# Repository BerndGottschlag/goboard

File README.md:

# GoBoard

This project contains the PCB design and the firmware for a compact modular
wireless mechanical keyboard.

## License

All hardware designes are licensed under the CERN Open Hardware License v1.2.

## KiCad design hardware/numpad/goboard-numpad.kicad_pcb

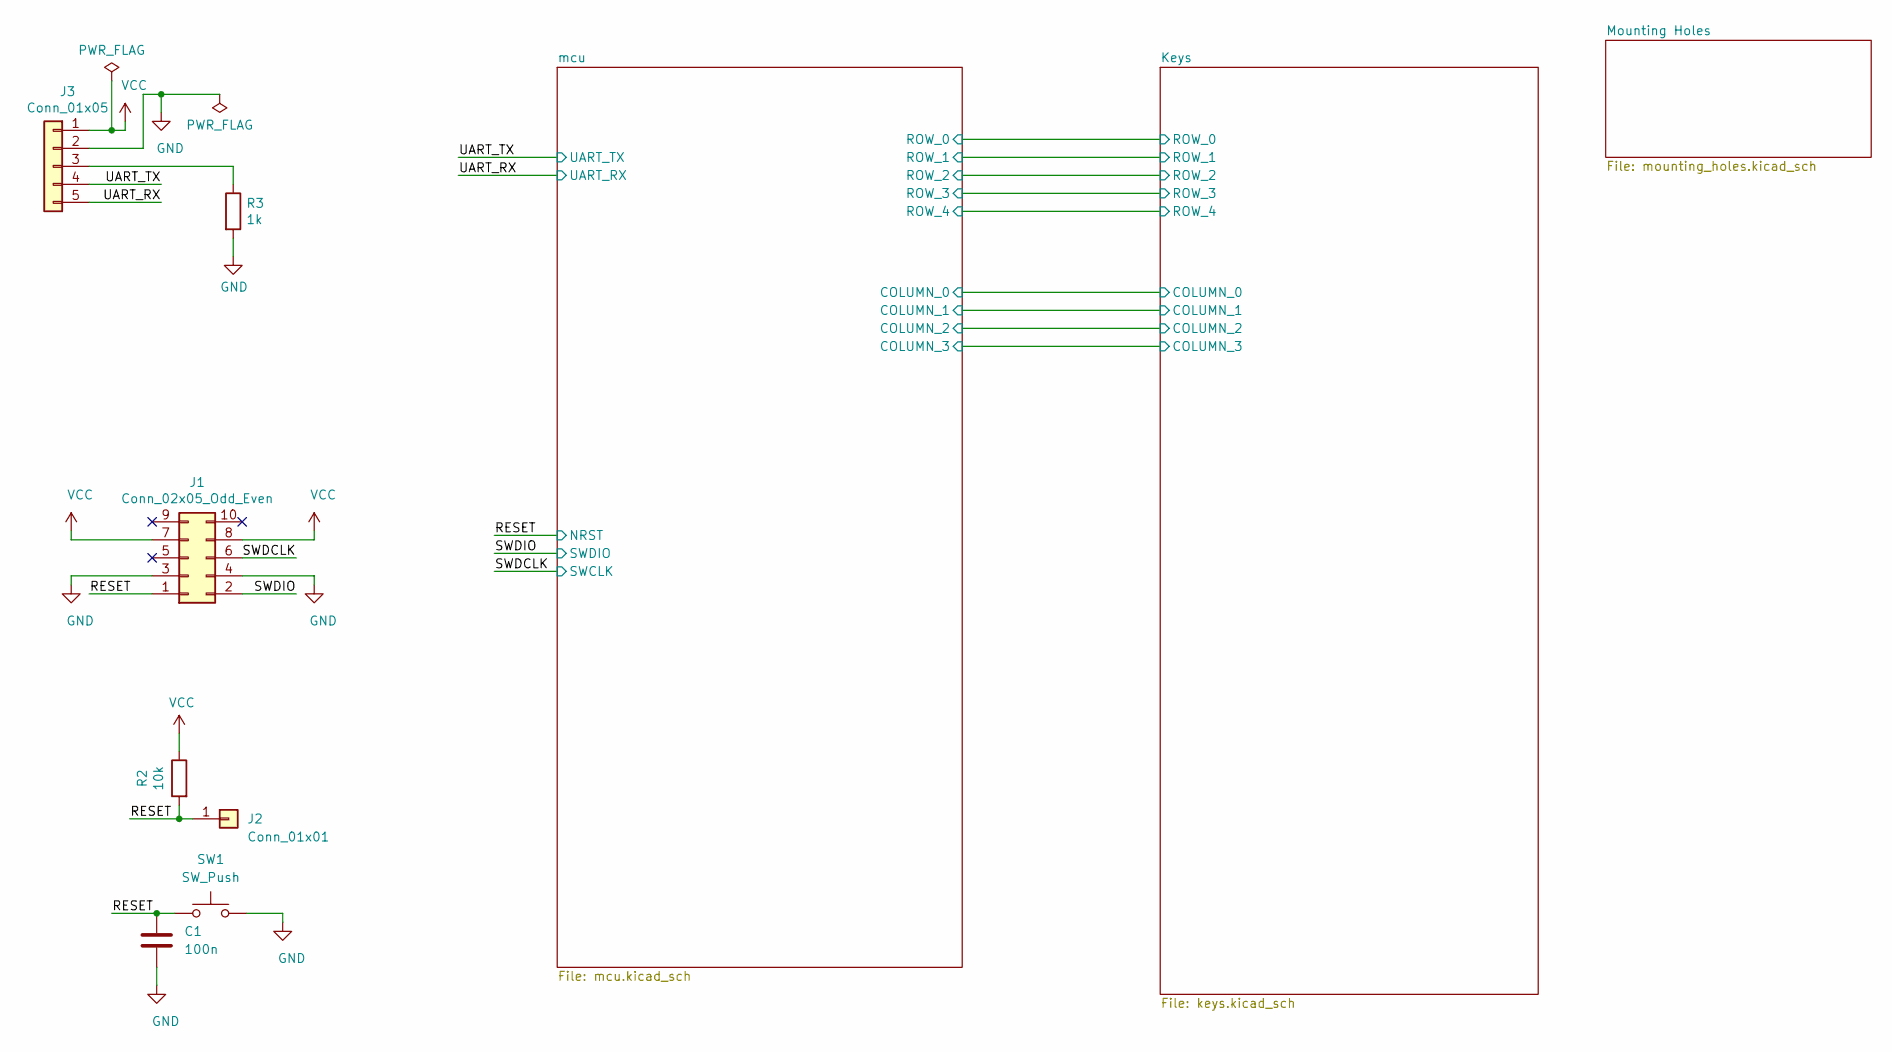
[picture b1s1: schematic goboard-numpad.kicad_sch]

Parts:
C1: 100n; C_0603_1608Metric_Pad1.08x0.95mm_HandSolder; Part Name AVX 0603YC104MAT4A; Mouser 581-0603YC104MAT4A
J1: Conn_02x05_Odd_Even; programming_port_st_link_clone_without_silkscreen_outline
J2: Conn_01x01; PinHeader_1x01_P2.54mm_Vertical
J3: Conn_01x05; PinHeader_1x05_P2.54mm_Vertical
R2: 10k; R_0603_1608Metric_Pad0.98x0.95mm_HandSolder
R3: 1k; R_0603_1608Metric_Pad0.98x0.95mm_HandSolder
SW1: SW_Push; SW_SPST_CK_RS282G05A3; Part Name PTS636 SM25 SMTR LFS; Mouser 611-PTS636SM25SMTRLF

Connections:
/RESET: C1.1, J1.1, J2.1, R2.2, SW1.1; also elsewhere on the board
/SWDCLK: J1.6; also elsewhere on the board
/SWDIO: J1.2; also elsewhere on the board
/UART_RX: J3.5; also elsewhere on the board
/UART_TX: J3.4; also elsewhere on the board
GND: C1.2, J1.3, J1.4, J3.2, R3.2, SW1.2; also elsewhere on the board
unnamed: J3.3, R3.1
VCC: J1.7, J1.8, J3.1, R2.1; also elsewhere on the board

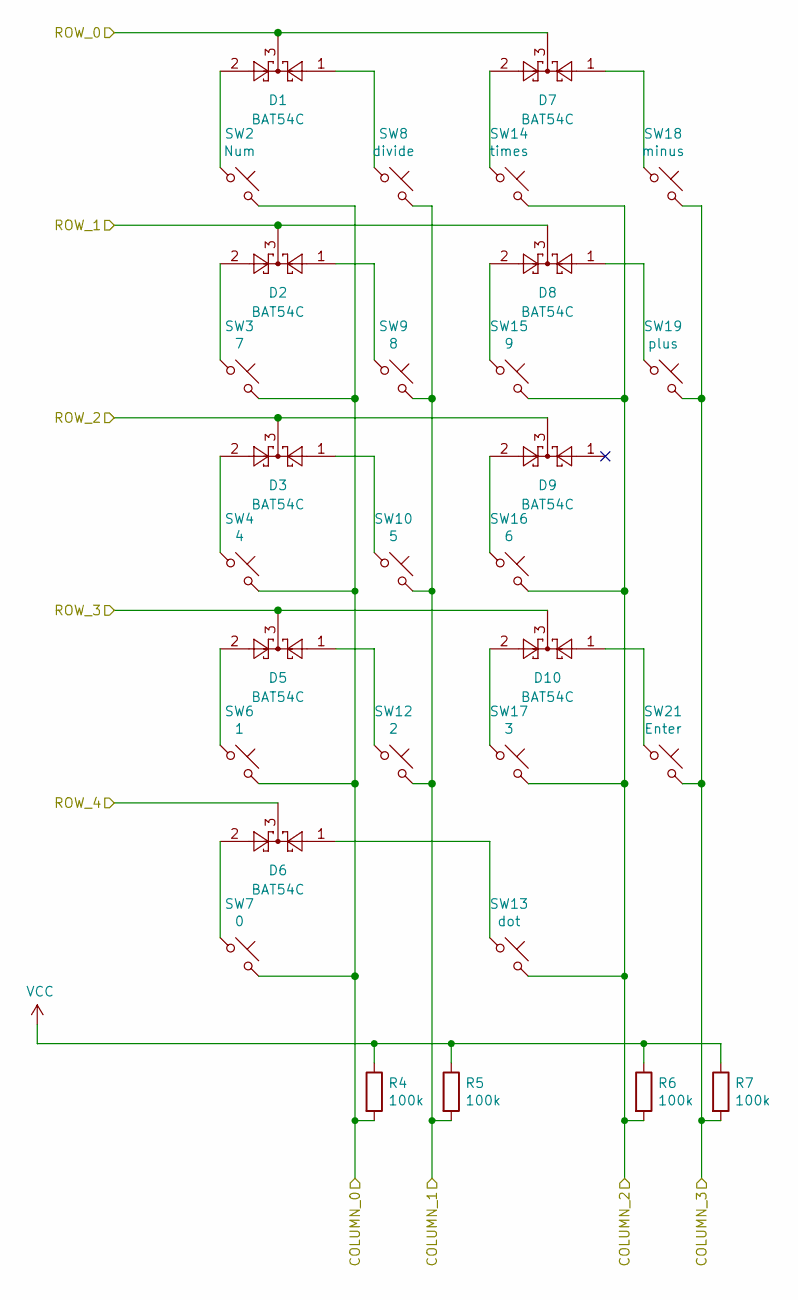
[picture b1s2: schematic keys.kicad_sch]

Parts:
D1, D2, D3, D5, D6, D7, D8, D9, D10: BAT54C; SOT-23; Part Name BAT54C; Mouser 241-BAT54C_R1_00001
R4, R5, R6, R7: 100k; R_0603_1608Metric_Pad0.98x0.95mm_HandSolder
SW2: Num; SW_Cherry_MX_1.00u_PCB; Part Name MX1A-E1NW; Mouser 540-MX1A-E1NW
SW3: 7; SW_Cherry_MX_1.00u_PCB; Part Name MX1A-E1NW; Mouser 540-MX1A-E1NW
SW4: 4; SW_Cherry_MX_1.00u_PCB; Part Name MX1A-E1NW; Mouser 540-MX1A-E1NW
SW6: 1; SW_Cherry_MX_1.00u_PCB; Part Name MX1A-E1NW; Mouser 540-MX1A-E1NW
SW7: 0; SW_Cherry_MX_2.00u_PCB; Part Name MX1A-E1NW; Mouser 540-MX1A-E1NW
SW8: divide; SW_Cherry_MX_1.00u_PCB; Part Name MX1A-E1NW; Mouser 540-MX1A-E1NW
SW9: 8; SW_Cherry_MX_1.00u_PCB; Part Name MX1A-E1NW; Mouser 540-MX1A-E1NW
SW10: 5; SW_Cherry_MX_1.00u_PCB; Part Name MX1A-E1NW; Mouser 540-MX1A-E1NW
SW12: 2; SW_Cherry_MX_1.00u_PCB; Part Name MX1A-E1NW; Mouser 540-MX1A-E1NW
SW13: dot; SW_Cherry_MX_1.00u_PCB; Part Name MX1A-E1NW; Mouser 540-MX1A-E1NW
SW14: times; SW_Cherry_MX_1.00u_PCB; Part Name MX1A-E1NW; Mouser 540-MX1A-E1NW
SW15: 9; SW_Cherry_MX_1.00u_PCB; Part Name MX1A-E1NW; Mouser 540-MX1A-E1NW
SW16: 6; SW_Cherry_MX_1.00u_PCB; Part Name MX1A-E1NW; Mouser 540-MX1A-E1NW
SW17: 3; SW_Cherry_MX_1.00u_PCB; Part Name MX1A-E1NW; Mouser 540-MX1A-E1NW
SW18: minus; SW_Cherry_MX_1.00u_PCB; Part Name MX1A-E1NW; Mouser 540-MX1A-E1NW
SW19: plus; SW_Cherry_MX_2.00u_PCB; Part Name MX1A-E1NW; Mouser 540-MX1A-E1NW
SW21: Enter; SW_Cherry_MX_2.00u_PCB; Part Name MX1A-E1NW; Mouser 540-MX1A-E1NW

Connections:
/Keys/COLUMN_0: R4.2, SW2.2, SW3.2, SW4.2, SW6.2, SW7.2; also elsewhere on the board
/Keys/COLUMN_1: R5.2, SW8.2, SW9.2, SW10.2, SW12.2; also elsewhere on the board
/Keys/COLUMN_2: R6.2, SW13.2, SW14.2, SW15.2, SW16.2, SW17.2; also elsewhere on the board
/Keys/COLUMN_3: R7.2, SW18.2, SW19.2, SW21.2; also elsewhere on the board
/Keys/ROW_0: D1.3, D7.3; also elsewhere on the board
/Keys/ROW_1: D2.3, D8.3; also elsewhere on the board
/Keys/ROW_2: D3.3, D9.3; also elsewhere on the board
/Keys/ROW_3: D5.3, D10.3; also elsewhere on the board
/Keys/ROW_4: D6.3; also elsewhere on the board
unnamed: D1.1, SW8.1
unnamed: D1.2, SW2.1
unnamed: D2.1, SW9.1
unnamed: D2.2, SW3.1
unnamed: D3.1, SW10.1
unnamed: D3.2, SW4.1
unnamed: D5.1, SW12.1
unnamed: D5.2, SW6.1
unnamed: D6.1, SW13.1
unnamed: D6.2, SW7.1
unnamed: D7.1, SW18.1
unnamed: D7.2, SW14.1
unnamed: D8.1, SW19.1
unnamed: D8.2, SW15.1
unnamed: D9.2, SW16.1
unnamed: D10.1, SW21.1
unnamed: D10.2, SW17.1
VCC: R4.1, R5.1, R6.1, R7.1; also elsewhere on the board

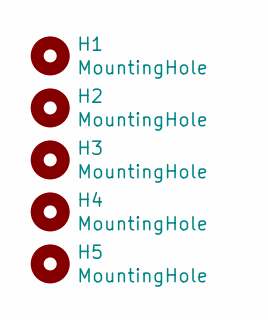
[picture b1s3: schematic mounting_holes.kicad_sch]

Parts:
H1, H2, H3, H4, H5: MountingHole; MountingHole_2.2mm_M2_Pad

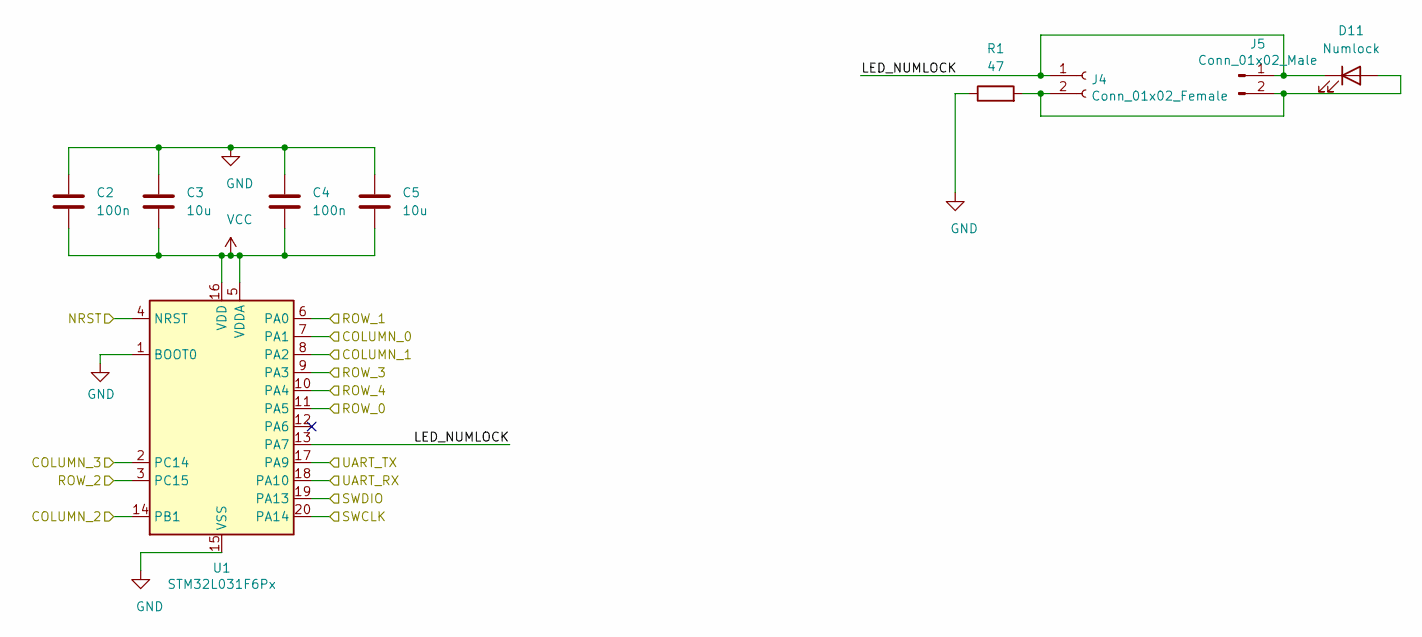
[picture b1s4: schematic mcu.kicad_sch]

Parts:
C2, C4: 100n; C_0603_1608Metric_Pad1.08x0.95mm_HandSolder; Part Name AVX 0603YC104MAT4A; Mouser 581-0603YC104MAT4A
C3, C5: 10u; C_0805_2012Metric; Part Name Samsung CL21A106KOQNNNG; Mouser 187-CL21A106KOQNNNG
D11: Numlock; D_0603_1608Metric_Pad1.05x0.95mm_HandSolder; Part Name 150060SS75000; Mouser 710-150060SS75000
J4: Conn_01x02_Female; PinSocket_1x02_P2.00mm_Vertical
J5: Conn_01x02_Male; PinSocket_1x02_P2.00mm_Vertical
R1: 47; R_0603_1608Metric_Pad0.98x0.95mm_HandSolder
U1: STM32L031F6Px; TSSOP-20_4.4x6.5mm_P0.65mm; Part Name STM32L031F6P7; Mouser 511-STM32L031F6P7

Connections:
/Keys/COLUMN_0: U1.7 (PA1); also elsewhere on the board
/Keys/COLUMN_1: U1.8 (PA2); also elsewhere on the board
/Keys/COLUMN_2: U1.14 (PB1); also elsewhere on the board
/Keys/COLUMN_3: U1.2 (PC14); also elsewhere on the board
/Keys/ROW_0: U1.11 (PA5); also elsewhere on the board
/Keys/ROW_1: U1.6 (PA0); also elsewhere on the board
/Keys/ROW_2: U1.3 (PC15); also elsewhere on the board
/Keys/ROW_3: U1.9 (PA3); also elsewhere on the board
/Keys/ROW_4: U1.10 (PA4); also elsewhere on the board
/RESET: U1.4 (NRST); also elsewhere on the board
/SWDCLK: U1.20 (PA14); also elsewhere on the board
/SWDIO: U1.19 (PA13); also elsewhere on the board
/UART_RX: U1.18 (PA10); also elsewhere on the board
/UART_TX: U1.17 (PA9); also elsewhere on the board
/mcu/LED_NUMLOCK: D11.1 (K), J4.1, J5.1, U1.13 (PA7)
GND: C2.1, C3.1, C4.1, C5.1, R1.1, U1.1 (BOOT0), U1.15 (VSS); also elsewhere on the board
unnamed: D11.2 (A), J4.2, J5.2, R1.2
VCC: C2.2, C3.2, C4.2, C5.2, U1.5 (VDDA), U1.16 (VDD); also elsewhere on the board

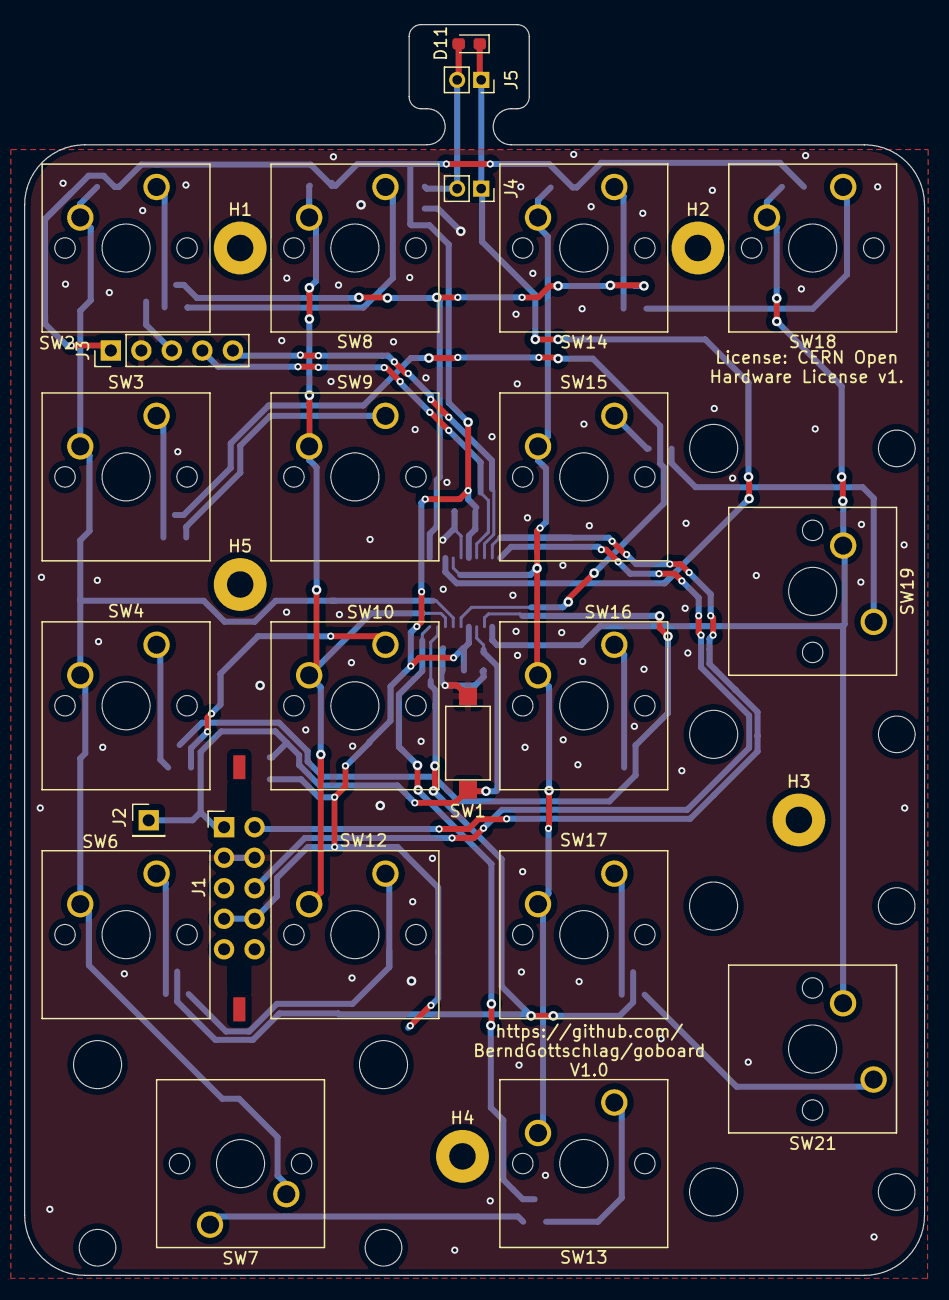
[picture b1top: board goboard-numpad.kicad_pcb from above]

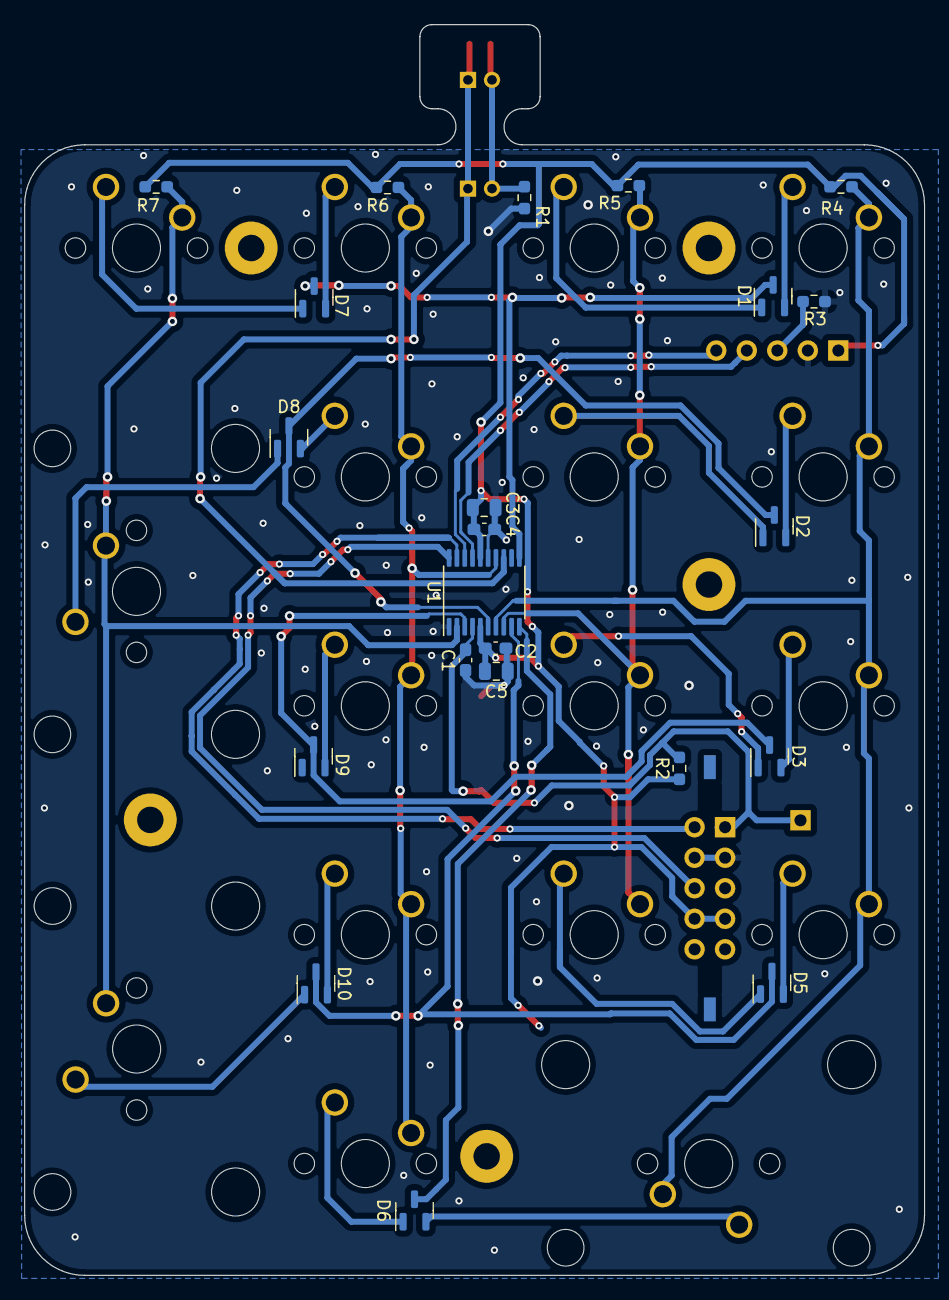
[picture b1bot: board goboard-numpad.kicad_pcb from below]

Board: 2 copper layers, 74.9 x 104.1 mm, 51 parts (22 on the bottom side), 36 nets.

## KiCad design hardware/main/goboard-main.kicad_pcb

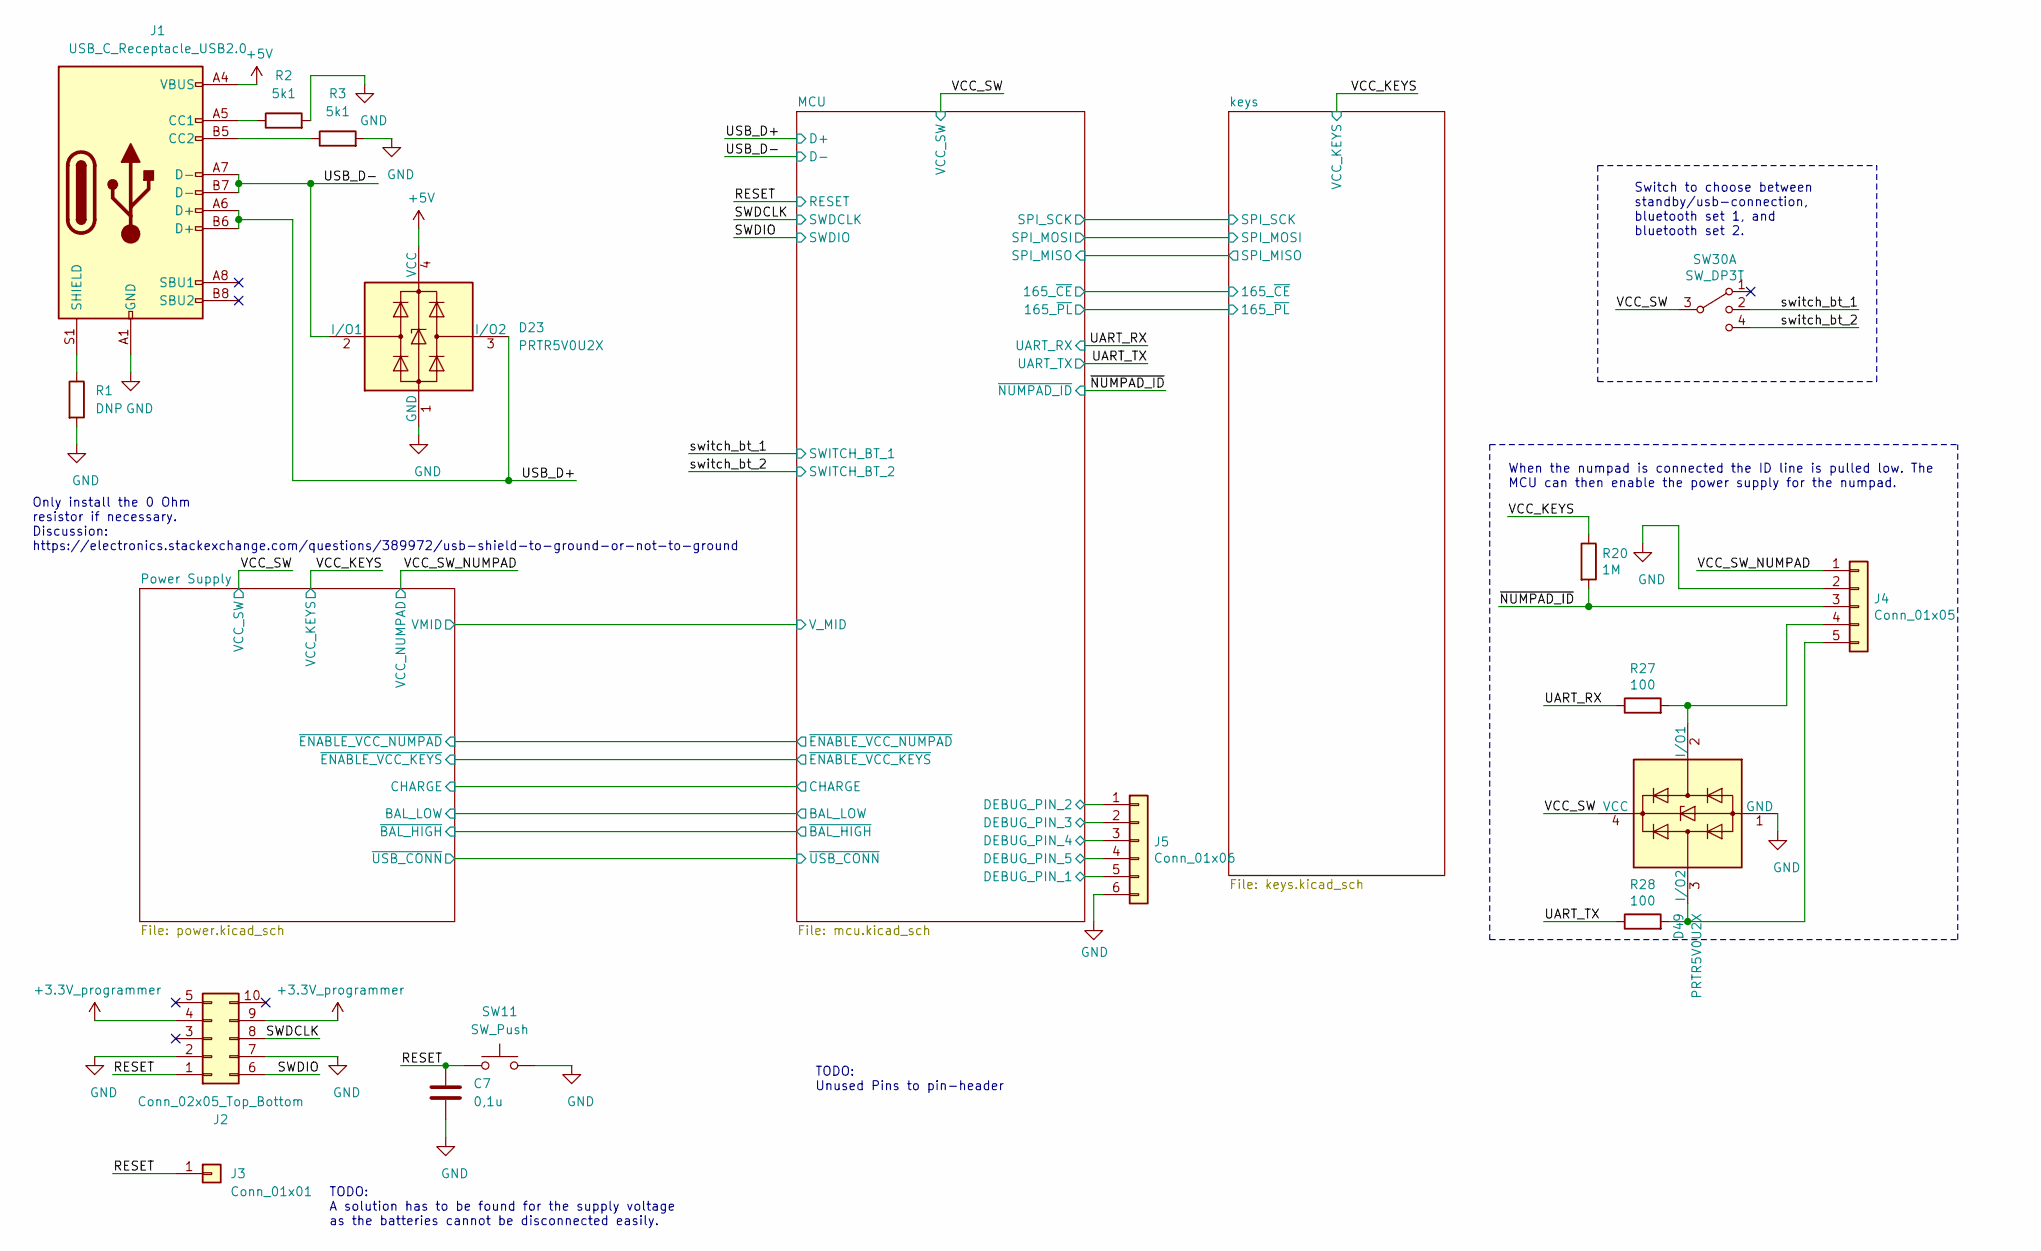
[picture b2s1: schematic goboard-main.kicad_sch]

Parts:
C7: 0,1u; C_0603_1608Metric_Pad1.08x0.95mm_HandSolder; Part Name 06033C104KAT4A; Mouser 581-06033C104KAT4A
D23, D49: PRTR5V0U2X; SOT-143; Part Name PRTR5V0U2X,215; Mouser 771-PRTR5V0U2X-T/R
J1: USB_C_Receptacle_USB2.0; USB_C_Receptale_JAE_DX07S016JA1R1500; Part Name DX07S016JA1R1500; Mouser 656-DX07S016JA1R1500
J2: Conn_02x05_Top_Bottom; programming_port_st_link_clone
J3: Conn_01x01; PinHeader_1x01_P2.54mm_Vertical
J4: Conn_01x05; PinHeader_1x05_P2.54mm_Vertical
J5: Conn_01x06; PinHeader_1x06_P2.54mm_Vertical
R1: DNP; R_0603_1608Metric_Pad0.98x0.95mm_HandSolder
R2, R3: 5k1; R_0603_1608Metric_Pad0.98x0.95mm_HandSolder
R20: 1M; R_0603_1608Metric_Pad0.98x0.95mm_HandSolder
R27, R28: 100; R_0603_1608Metric_Pad0.98x0.95mm_HandSolder
SW11: SW_Push; SW_SPST_CK_RS282G05A3; Part Name PTS636 SM25 SMTR LFS; Mouser 611-PTS636SM25SMTRLF
SW30: SW_DP3T; EG2315A; Part Name EG2315A; Mouser 612-EG2315A

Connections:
+5V: D23.4 (VCC), J1.A4 (VBUS), J1.A9 (VBUS), J1.B4 (VBUS), J1.B9 (VBUS); also elsewhere on the board
/MCU/DEBUG_PIN_1: J5.5; also elsewhere on the board
/MCU/DEBUG_PIN_2: J5.1; also elsewhere on the board
/MCU/DEBUG_PIN_3: J5.2; also elsewhere on the board
/MCU/DEBUG_PIN_4: J5.3; also elsewhere on the board
/MCU/DEBUG_PIN_5: J5.4; also elsewhere on the board
/RESET: C7.1, J2.1, J3.1, SW11.1; also elsewhere on the board
/SWDCLK: J2.8; also elsewhere on the board
/SWDIO: J2.6; also elsewhere on the board
/UART_RX: R27.1; also elsewhere on the board
/UART_TX: R28.1; also elsewhere on the board
/USB_D+: D23.3 (I/O2), J1.A6 (D+), J1.B6 (D+); also elsewhere on the board
/USB_D-: D23.2 (I/O1), J1.A7 (D-), J1.B7 (D-); also elsewhere on the board
/VCC_KEYS: R20.1; also elsewhere on the board
/VCC_SW: D49.4 (VCC), SW30.3; also elsewhere on the board
/VCC_SW_NUMPAD: J4.1; also elsewhere on the board
/switch_bt_1: SW30.2; also elsewhere on the board
/switch_bt_2: SW30.4; also elsewhere on the board
/~NUMPAD_ID: J4.3, R20.2; also elsewhere on the board
GND: C7.2, D23.1 (GND), D49.1 (GND), J1.A1 (GND), J1.A12 (GND), J1.B1 (GND), J1.B12 (GND), J2.2, J2.7, J4.2, J5.6, R1.2, R2.2, R3.2, SW11.2; also elsewhere on the board
unnamed: D49.2 (I/O1), J4.4, R27.2
unnamed: D49.3 (I/O2), J4.5, R28.2
unnamed: J1.A5 (CC1), R2.1
unnamed: J1.B5 (CC2), R3.1
unnamed: J1.S1 (SHIELD), R1.1

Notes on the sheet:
Only install the 0 Ohm resistor if necessary. Discussion: https://electronics.stackexchange.com/questions/389972/usb-shield-to-ground-or-not-to-ground
TODO: A solution has to be found for the supply voltage as the batteries cannot be disconnected easily.
TODO: Unused Pins to pin-header
When the numpad is connected the ID line is pulled low. The MCU can then enable the power supply for the numpad.
Switch to choose between standby/usb-connection, bluetooth set 1, and bluetooth set 2.

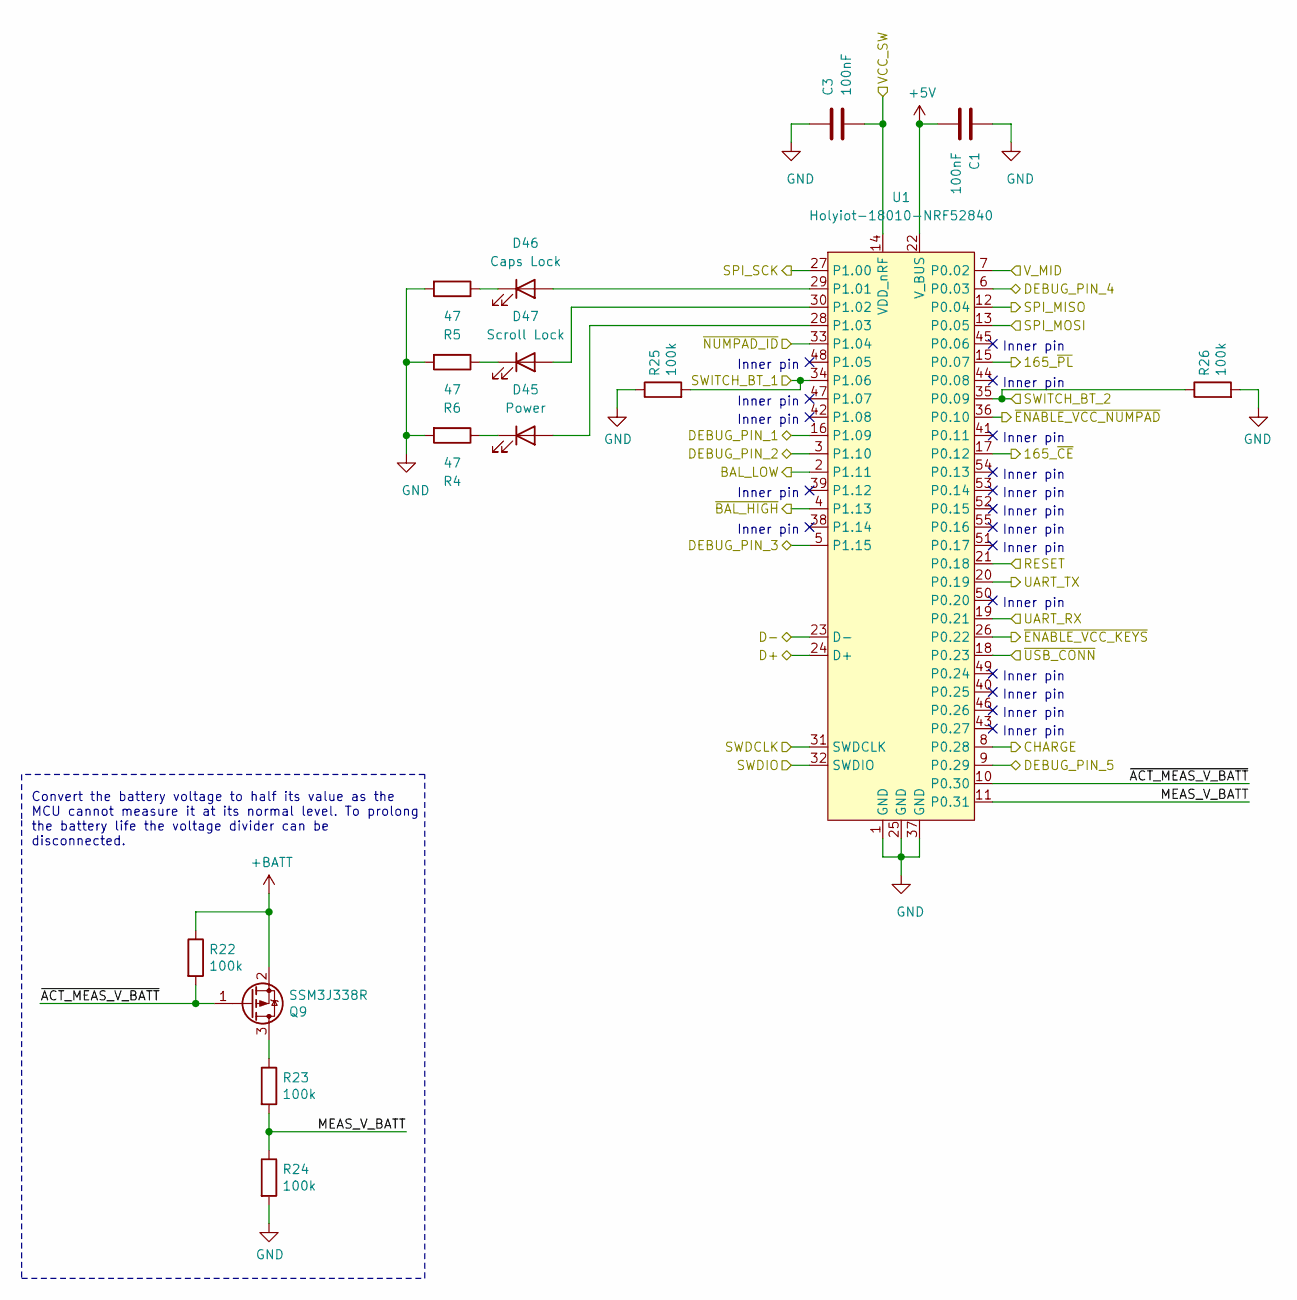
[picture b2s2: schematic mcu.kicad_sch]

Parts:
C1, C3: 100nF; C_0603_1608Metric_Pad1.08x0.95mm_HandSolder; Part Name 06033C104KAT4A; Mouser 581-06033C104KAT4A
D45: Power; D_0603_1608Metric_Pad1.05x0.95mm_HandSolder; Part Name 150060SS75000; Mouser 710-150060SS75000
D46: Caps Lock; D_0603_1608Metric_Pad1.05x0.95mm_HandSolder; Part Name 150060SS75000; Mouser 710-150060SS75000
D47: Scroll Lock; D_0603_1608Metric_Pad1.05x0.95mm_HandSolder; Part Name 150060SS75000; Mouser 710-150060SS75000
Q9: SSM3J338R; SOT-23_Handsoldering; Part Name Toshiba SSM3J338R; Mouser 757-SSM3J338RLF
R4, R5, R6: 47; R_0603_1608Metric_Pad0.98x0.95mm_HandSolder
R22, R23, R24, R25, R26: 100k; R_0603_1608Metric_Pad0.98x0.95mm_HandSolder
U1: Holyiot-18010-NRF52840

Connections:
+5V: C1.2, U1.22 (V_BUS); also elsewhere on the board
+BATT: Q9.2 (S), R22.1; also elsewhere on the board
/MCU/165_~CE: U1.17 (P0.12); also elsewhere on the board
/MCU/165_~PL: U1.15 (P0.07); also elsewhere on the board
/MCU/BAL_LOW: U1.2 (P1.11); also elsewhere on the board
/MCU/CHARGE: U1.8 (P0.28); also elsewhere on the board
/MCU/DEBUG_PIN_1: U1.16 (P1.09); also elsewhere on the board
/MCU/DEBUG_PIN_2: U1.3 (P1.10); also elsewhere on the board
/MCU/DEBUG_PIN_3: U1.5 (P1.15); also elsewhere on the board
/MCU/DEBUG_PIN_4: U1.6 (P0.03); also elsewhere on the board
/MCU/DEBUG_PIN_5: U1.9 (P0.29); also elsewhere on the board
/MCU/MEAS_V_BATT: R23.2, R24.1, U1.11 (P0.31)
/MCU/SPI_MISO: U1.12 (P0.04); also elsewhere on the board
/MCU/SPI_MOSI: U1.13 (P0.05); also elsewhere on the board
/MCU/SPI_SCK: U1.27 (P1.00); also elsewhere on the board
/MCU/V_MID: U1.7 (P0.02); also elsewhere on the board
/MCU/~ACT_MEAS_V_BATT: Q9.1 (G), R22.2, U1.10 (P0.30)
/MCU/~BAL_HIGH: U1.4 (P1.13); also elsewhere on the board
/MCU/~ENABLE_VCC_KEYS: U1.26 (P0.22); also elsewhere on the board
/MCU/~ENABLE_VCC_NUMPAD: U1.36 (P0.10); also elsewhere on the board
/MCU/~USB_CONN: U1.18 (P0.23); also elsewhere on the board
/RESET: U1.21 (P0.18); also elsewhere on the board
/SWDCLK: U1.31 (SWDCLK); also elsewhere on the board
/SWDIO: U1.32 (SWDIO); also elsewhere on the board
/UART_RX: U1.19 (P0.21); also elsewhere on the board
/UART_TX: U1.20 (P0.19); also elsewhere on the board
/USB_D+: U1.24 (D+); also elsewhere on the board
/USB_D-: U1.23 (D-); also elsewhere on the board
/VCC_SW: C3.2, U1.14 (VDD_nRF); also elsewhere on the board
/switch_bt_1: R25.2, U1.34 (P1.06); also elsewhere on the board
/switch_bt_2: R26.1, U1.35 (P0.09); also elsewhere on the board
/~NUMPAD_ID: U1.33 (P1.04); also elsewhere on the board
GND: C1.1, C3.1, R4.2, R5.2, R6.2, R24.2, R25.1, R26.2, U1.1 (GND), U1.25 (GND), U1.37 (GND); also elsewhere on the board
unnamed: D45.1 (K), R4.1
unnamed: D45.2 (A), U1.28 (P1.03)
unnamed: D46.1 (K), R5.1
unnamed: D46.2 (A), U1.29 (P1.01)
unnamed: D47.1 (K), R6.1
unnamed: D47.2 (A), U1.30 (P1.02)
unnamed: Q9.3 (D), R23.1

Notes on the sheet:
Convert the battery voltage to half its value as the MCU cannot measure it at its normal level. To prolong the battery life the voltage divider can be disconnected.
Inner pin

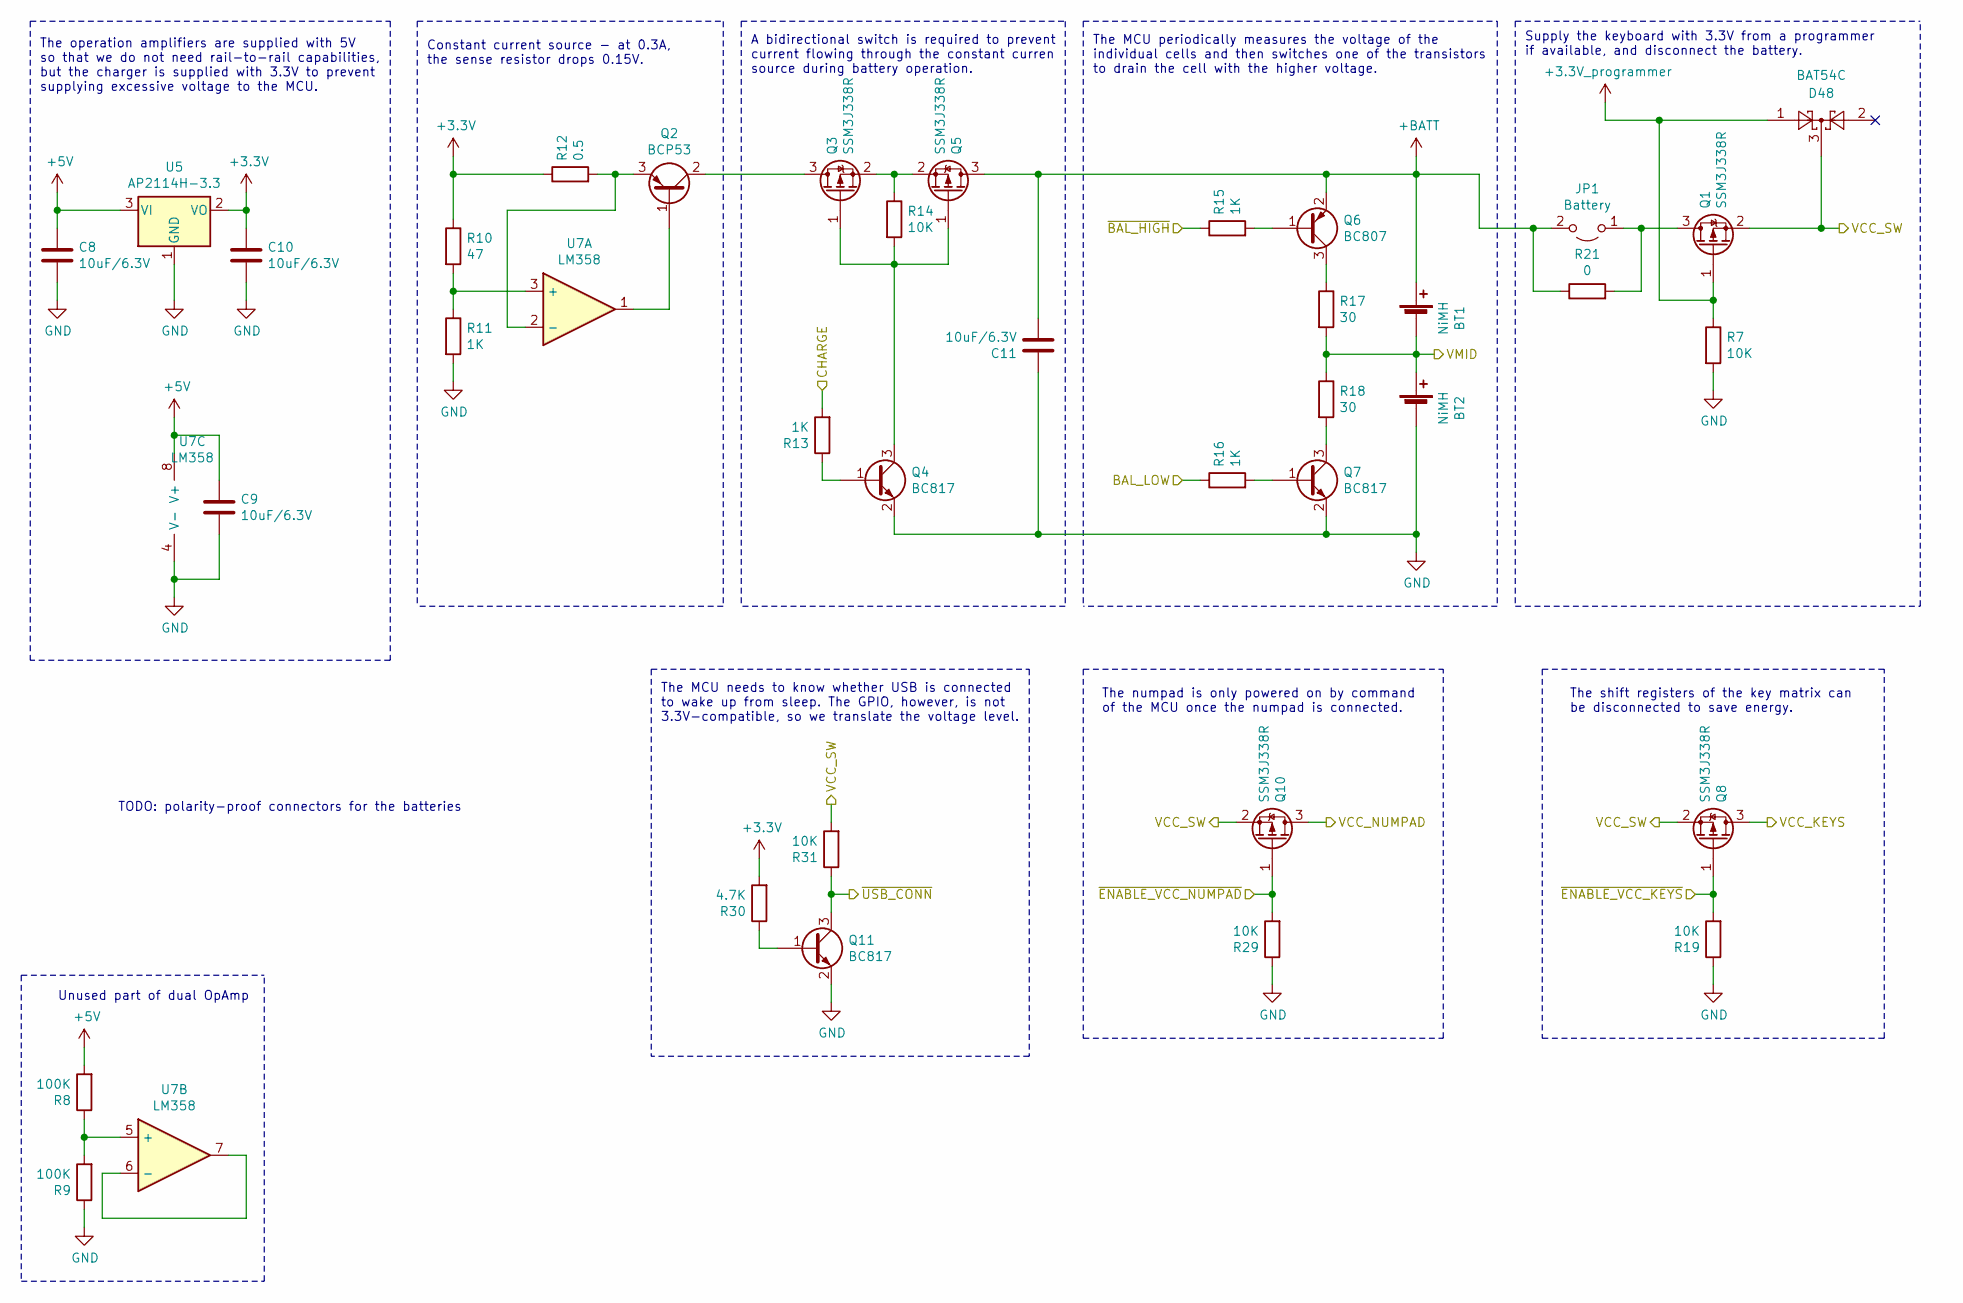
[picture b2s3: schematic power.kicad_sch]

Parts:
BT1, BT2: NiMH; JST_XH_S2B-XH-A_1x02_P2.50mm_Horizontal
C8, C9, C10, C11: 10uF/6.3V; C_0805_2012Metric; Part Name Taiyo Yuden LMK212F106ZG-T; Mouser 963-LMK212F106ZG-T
D48: BAT54C; SOT-23; Part Name BAT54A; Mouser 241-BAT54A_R1_00001
JP1: Battery; PinHeader_1x02_P2.54mm_Horizontal
Q1, Q3, Q5, Q8, Q10: SSM3J338R; SOT-23_Handsoldering; Part Name Toshiba SSM3J338R; Mouser 757-SSM3J338RLF
Q2: BCP53; SOT-223; Part Name Nexperia BCP53TF; Mouser 771-BCP53TF
Q4, Q7, Q11: BC817; SOT-23
Q6: BC807; SOT-23
R7, R14, R19, R29, R31: 10K; R_0603_1608Metric
R8, R9: 100K; R_0603_1608Metric
R10: 47; R_0603_1608Metric
R11, R13, R15, R16: 1K; R_0603_1608Metric
R12: 0.5; R_1206_3216Metric; Part Name Ohmite KDV12FR510ET; Mouser 588-KDV12FR510ET
R17, R18: 30; R_0603_1608Metric
R21: 0; R_0603_1608Metric_Pad0.98x0.95mm_HandSolder
R30: 4.7K; R_0603_1608Metric
U5: AP2114H-3.3; SOT-223-3_TabPin2; Part Name Diodes Inc AP2114H-3.3TRG1; Mouser 621-AP2114H-3.3TRG1
U7: LM358

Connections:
+5V: C8.1, C9.1, R8.2, U5.3 (VI), U7.8 (V+); also elsewhere on the board
+BATT: BT1.1 (+), C11.2, JP1.2 (B), Q5.3 (D), Q6.2 (E), R21.1; also elsewhere on the board
/MCU/BAL_LOW: R16.1; also elsewhere on the board
/MCU/CHARGE: R13.2; also elsewhere on the board
/MCU/V_MID: BT1.2 (-), BT2.1 (+), R17.2, R18.1; also elsewhere on the board
/MCU/~BAL_HIGH: R15.1; also elsewhere on the board
/MCU/~ENABLE_VCC_KEYS: Q8.1 (G), R19.2; also elsewhere on the board
/MCU/~ENABLE_VCC_NUMPAD: Q10.1 (G), R29.2; also elsewhere on the board
/MCU/~USB_CONN: Q11.3 (C), R31.1; also elsewhere on the board
/VCC_KEYS: Q8.3 (D); also elsewhere on the board
/VCC_SW: D48.3, Q1.2 (S), Q8.2 (S), Q10.2 (S), R31.2; also elsewhere on the board
/VCC_SW_NUMPAD: Q10.3 (D); also elsewhere on the board
GND: BT2.2 (-), C8.2, C9.2, C10.2, C11.1, Q4.2 (E), Q7.2 (E), Q11.2 (E), R7.2, R9.1, R11.2, R19.1, R29.1, U5.1 (GND), U7.4 (V-); also elsewhere on the board
unnamed: JP1.1 (A), Q1.3 (D), R21.2
unnamed: Q2.1 (B), U7.1
unnamed: Q2.2 (C), Q2.4 (C), Q3.3 (D)
unnamed: Q2.3 (E), R12.2, U7.2 (-)
unnamed: Q3.1 (G), Q4.3 (C), Q5.1 (G), R14.2
unnamed: Q3.2 (S), Q5.2 (S), R14.1
unnamed: Q4.1 (B), R13.1
unnamed: Q6.1 (B), R15.2
unnamed: Q6.3 (C), R17.1
unnamed: Q7.1 (B), R16.2
unnamed: Q7.3 (C), R18.2
unnamed: Q11.1 (B), R30.1
unnamed: R8.1, R9.2, U7.5 (+)
unnamed: R10.2, R11.1, U7.3 (+)
unnamed: U7.6 (-), U7.7

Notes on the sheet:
The operation amplifiers are supplied with 5V so that we do not need rail-to-rail capabilities, but the charger is supplied with 3.3V to prevent supplying excessive voltage to the MCU.
Unused part of dual OpAmp
Constant current source - at 0.3A, the sense resistor drops 0.15V.
TODO: polarity-proof connectors for the batteries
The MCU needs to know whether USB is connected to wake up from sleep. The GPIO, however, is not 3.3V-compatible, so we translate the voltage level.
A bidirectional switch is required to prevent current flowing through the constant curren source during battery operation.
The MCU periodically measures the voltage of the individual cells and then switches one of the transistors to drain the cell with the higher voltage.
The numpad is only powered on by command of the MCU once the numpad is connected.
Supply the keyboard with 3.3V from a programmer if available, and disconnect the battery.
The shift registers of the key matrix can be disconnected to save energy.

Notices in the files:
hardware/numpad/goboard-numpad.kicad_pcb:
License: CERN Open
Hardware License v1.
